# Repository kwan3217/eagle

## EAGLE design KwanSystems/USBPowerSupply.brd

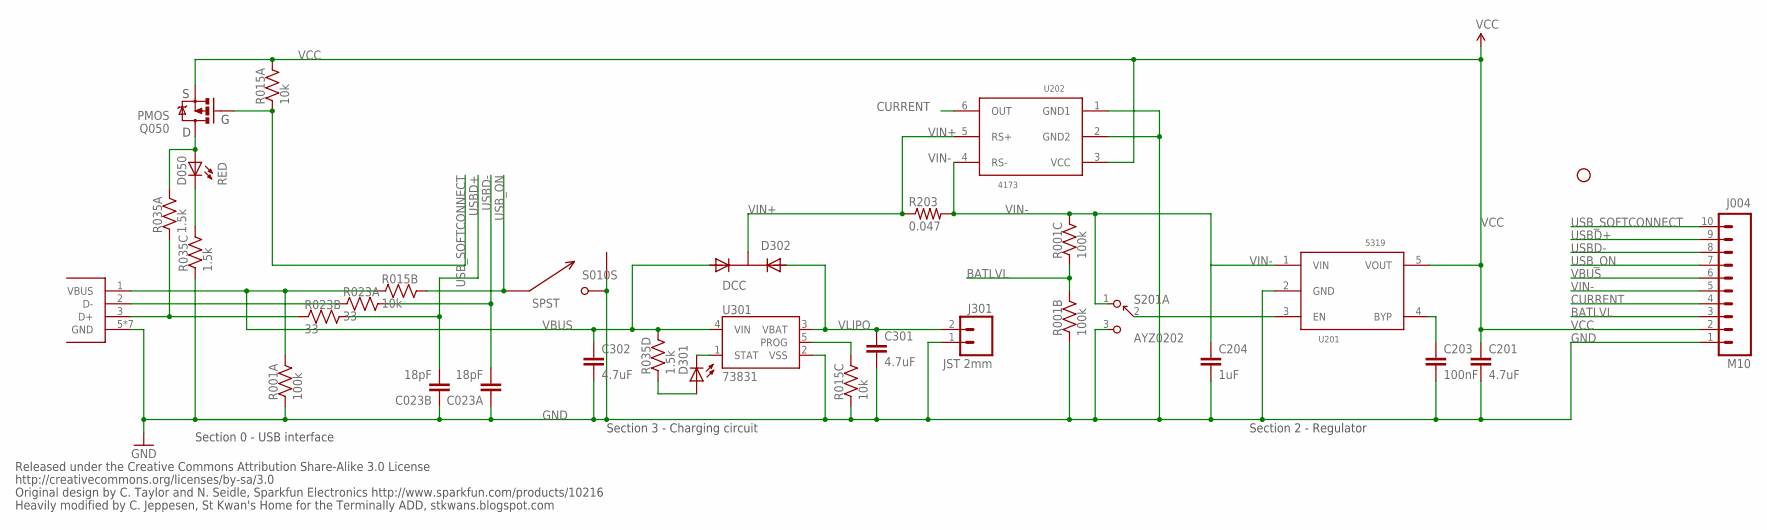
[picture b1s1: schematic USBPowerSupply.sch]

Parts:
C023: 18pF; CKCM25
C201, C301, C302: 4.7uF; 0402-CAP
C203: 100nF; 0402-CAP
C204: 1uF; 0402-CAP
D050, D301: RED; LED-0603
D302: DCC; SOT-23-3
J001: USB_MICROB_JSTGCT; USB_MICROB_3075
J004: M10; 1X10
J301: JST 2mm; JST-2-SMD
JP1: STAND-OFF
Q050: PMOS; SOT23-3
R001: 100k; CRA04
R015: 10k; CRA04
R023: 33; CRA02
R035: 1.5k; CRA04
R203: 0.047; 0402-RES
S010: SPST; B3U-1100P
S201: AYZ0202
U201: 5319; SOT-23-5
U202: 4173; SOT-23-6
U301: 73831; SOT23-5

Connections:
BATLVL: J004.3, R001.3 (1), R001.7 (2)
CONN_D+: J001.3 (D+), R023.2 (1), R035.1
CONN_D-: J001.2 (D-), R023.1
CURRENT: J004.4, U202.6 (OUT)
GND: C023.1, C023.2 (1), C201.2, C203.2, C204.2, C301.2, C302.2, J001.5 (GND), J001.P$1 (GND), J001.P$2 (GND), J001.P$3 (GND), J001.P$4 (GND), J001.P$8 (GND), J001.P$10 (GND), J004.1, J301.1, R001.1, R001.2 (1), R015.3 (1), R035.3 (1), S010.P$2 (2), S010.P$3 (1), S201.3, U201.2 (GND), U202.1 (GND1), U202.2 (GND2), U301.2 (VSS)
unnamed: D301.A, R035.4 (1)
unnamed: R015.6 (2), U301.5 (PROG)
unnamed: D301.C, U301.1 (STAT)
unnamed: S201.2, U201.3 (EN)
unnamed: D050.A, Q050.3 (D), R035.8 (2)
unnamed: D050.C, R035.6 (2)
unnamed: C203.1, U201.4 (BYP)
USBD+: C023.3 (2), J004.9, R023.3 (2)
USBD-: C023.4 (2), J004.8, R023.4 (2)
USB_ON: J004.7, R015.7 (2), S010.P$1 (1)
USB_SOFTCONNECT: J004.10, Q050.1 (G), R015.1
VBUS: C302.1, D302.1 (A1), J001.1 (VBUS), J004.6, R001.8 (2), R015.2 (1), R035.5 (2), U301.4 (VIN)
VCC: C201.1, J004.2, Q050.2 (S), R015.8 (2), U201.5 (VOUT), U202.3 (VCC)
VIN+: D302.3 (K), R203.1, U202.5 (RS+)
VIN-: C204.1, J004.5, R001.6 (2), R203.2, S201.1, U201.1 (VIN), U202.4 (RS-)
VLIPO: C301.1, D302.2 (A2), J301.2, U301.3 (VBAT)

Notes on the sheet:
Section 2 - Regulator
Section 3 - Charging circuit
Section 0 - USB interface
Released under the Creative Commons Attribution Share-Alike 3.0 License
http://creativecommons.org/licenses/by-sa/3.0
Original design by C. Taylor and N. Seidle, Sparkfun Electronics http://www.sparkfun.com/products/10216
Heavily modified by C. Jeppesen, St Kwan's Home for the Terminally ADD, stkwans.blogspot.com

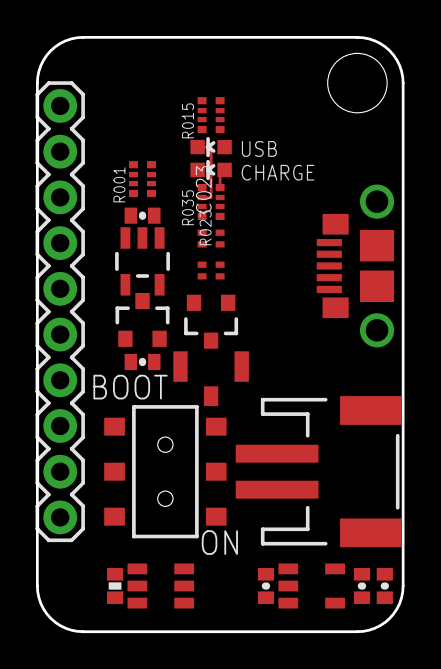
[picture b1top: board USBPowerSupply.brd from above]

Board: 2 copper layers, 20.3 x 33.0 mm, 24 parts (0 on the bottom side), 21 nets.

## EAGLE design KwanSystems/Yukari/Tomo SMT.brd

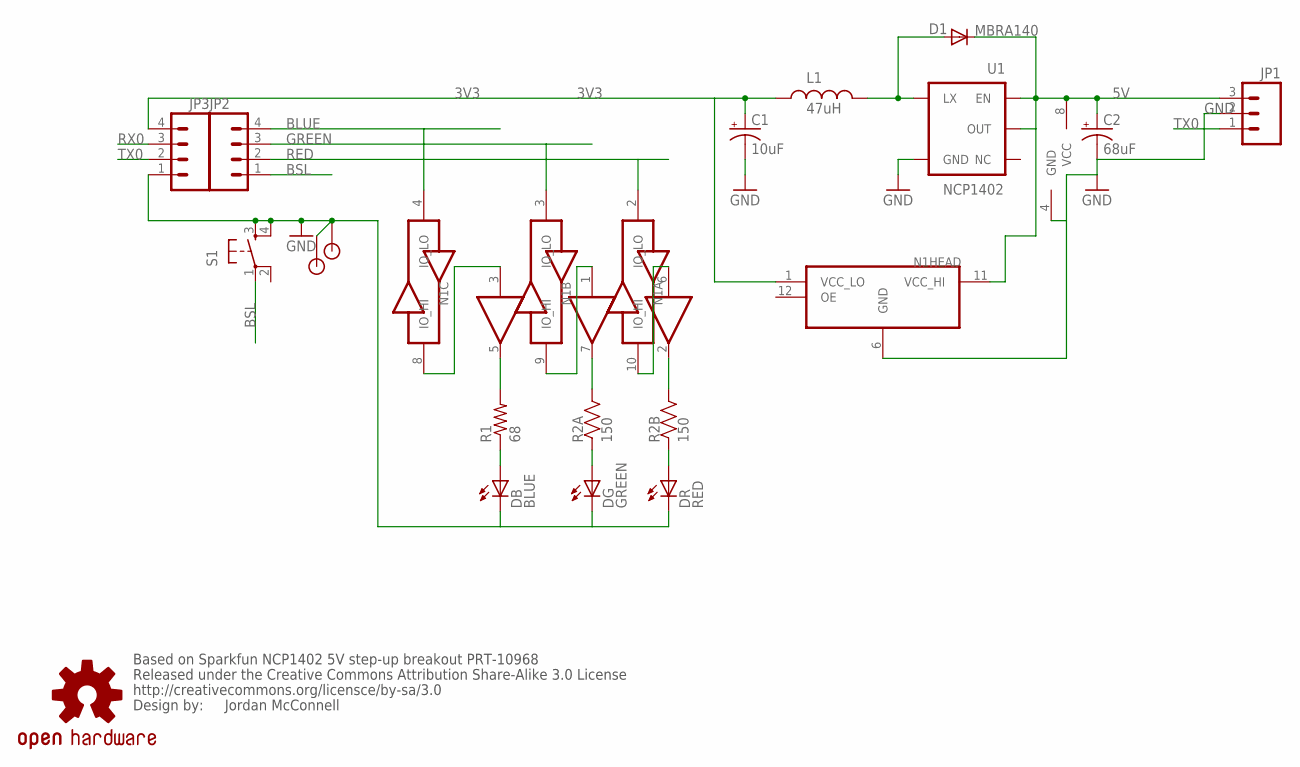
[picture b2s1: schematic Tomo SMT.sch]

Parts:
C1: 10uF; EIA3216
C2: 68uF; EIA3528
D1: MBRA140; SMA-DIODE
DB: BLUE; LED5MM
DG: GREEN; LED5MM
DR: RED; LED5MM
JP1: M03PTH; 1X03
JP2, JP3: M04PTH; 1X04
L1: 47uH; RADIAL_5MM
N1: TXB0104RUT; R-PUQFN-N12
R1: 68; 0402-RES
R2: 150; CRA02
S1: TAC_SWITCHPTH; TACTILE-PTH
U1: NCP1402; SOT23-5
U$1: OSHW-LOGOL; OSHW-LOGO-L
U$2: 743G34; DCT
U$3, U$4: STANDOFF

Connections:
3V3: C1.A (+), JP3.4, L1.1, N1.1 (VCC_LO)
5V: C2.A (+), D1.C, JP1.3, N1.11 (VCC_HI), U1.1 (EN), U1.2 (OUT), U$2.8 (VCC)
BLUE: JP2.4, N1.4 (IO_LO)
BSL: JP2.1, S1.1
GND: C1.C (-), C2.C (-), DB.K (C), DG.K (C), DR.K (C), JP1.2, JP3.1, N1.6 (GND), S1.3, S1.4, U1.4 (GND), U$2.4 (GND), U$3.P$1, U$4.P$1
GREEN: JP2.3, N1.3 (IO_LO)
unnamed: R1.2, U$2.5 (OUT)
unnamed: DB.A, R1.1
unnamed: D1.A, L1.2, U1.5 (LX)
unnamed: DG.A, R2.1
unnamed: R2.4 (2), U$2.7 (OUT)
unnamed: R2.3 (2), U$2.2 (OUT)
unnamed: DR.A, R2.2 (1)
unnamed: N1.8 (IO_HI), U$2.3 (IN)
unnamed: N1.9 (IO_HI), U$2.1 (IN)
unnamed: N1.10 (IO_HI), U$2.6 (IN)
RED: JP2.2, N1.2 (IO_LO)
RX0: JP3.3
TX0: JP1.1, JP3.2

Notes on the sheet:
Jordan McConnell
Based on Sparkfun NCP1402 5V step-up breakout PRT-10968
Released under the Creative Commons Attribution Share-Alike 3.0 License
http://creativecommons.org/licensce/by-sa/3.0
Design by:

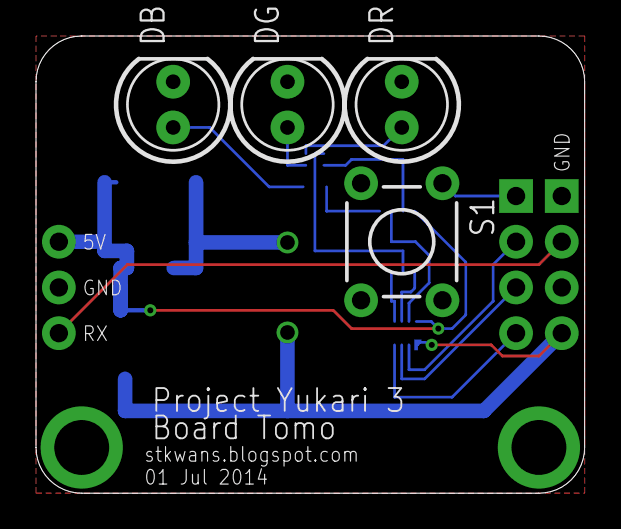
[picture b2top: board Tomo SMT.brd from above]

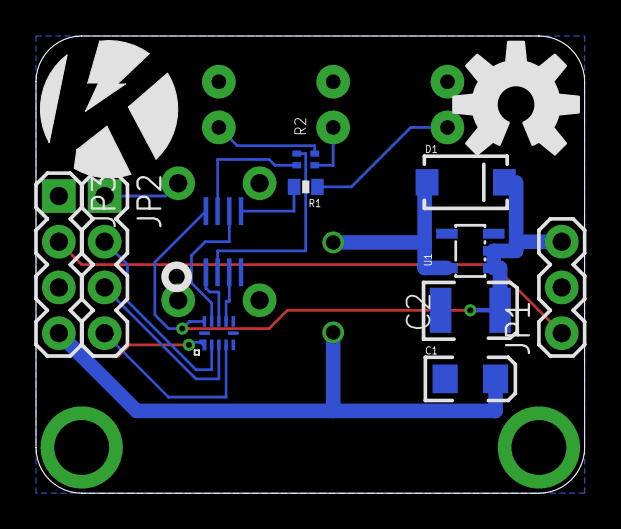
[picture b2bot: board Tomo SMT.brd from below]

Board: 2 copper layers, 30.5 x 25.4 mm, 20 parts (14 on the bottom side), 18 nets.

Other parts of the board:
U$7: KWAN_CIRCLE

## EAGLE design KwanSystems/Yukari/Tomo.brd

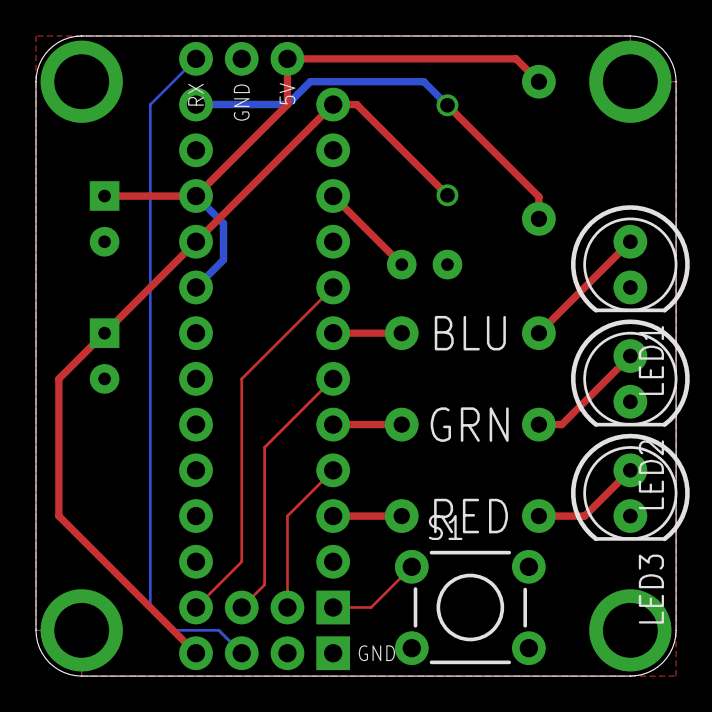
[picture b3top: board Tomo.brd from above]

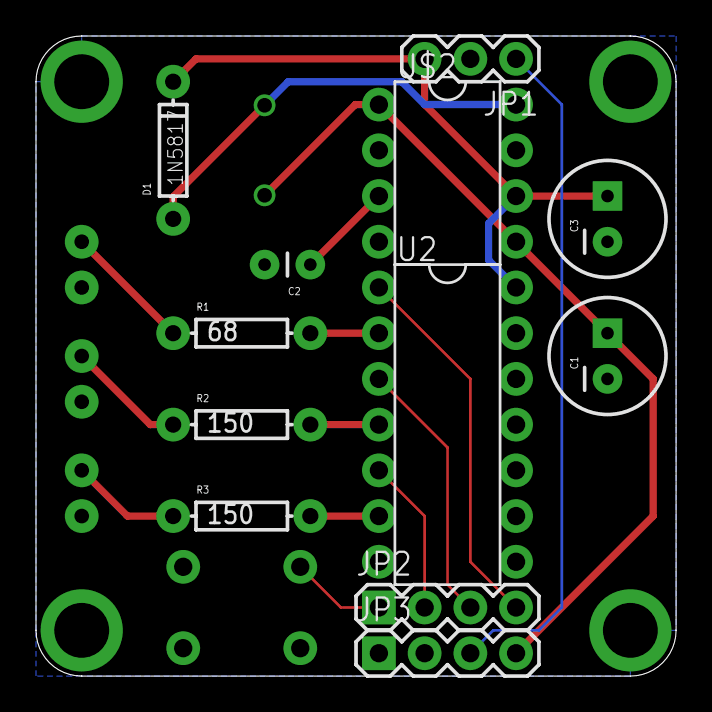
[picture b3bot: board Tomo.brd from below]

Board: 2 copper layers, 35.6 x 35.6 mm, 23 parts (13 on the bottom side), 16 nets.

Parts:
C1: 150uF; CPOL-RADIAL-100UF-25V
C2: 100nF; CAP-PTH-SMALL
C3: 100uF; CPOL-RADIAL-100UF-25V
D1: 1N5817; DIODE-1N4148
JP1: 1X03
JP2, JP3: 1X04
L1: 22uH; RADIAL_5MM
LED1: BLUE; LED5MM
LED2: GREEN; LED5MM
LED3: RED; LED5MM
R1: 68; AXIAL-0.3
R2, R3: 150; AXIAL-0.3
S1: TACTILE-PTH
U2: 741034; DIL-14
U$1: OSHW-LOGOL; OSHW-LOGO-L
U$2: MAX756; DIL-8
U$3, U$4, U$5, U$6: STANDOFF
U$7: KWAN_CIRCLE

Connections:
3V3: C1.1, JP3.4, L1.1, U$2.1, U$2.5
5V: C3.1, D1.C, JP1.3, U2.14, U$2.6
BLUE: JP2.4, U2.1
BSL: JP2.1, S1.1
GND: C1.2, C2.2, C3.2, JP1.2, JP3.1, LED1.K, LED2.K, LED3.K, S1.3, S1.4, U2.7, U2.9, U2.11, U2.13, U$2.2, U$2.7, U$3.P$1, U$4.P$1, U$5.P$1, U$6.P$1
GREEN: JP2.3, U2.3
unnamed: LED1.A, R1.P$1
unnamed: LED2.A, R2.P$1
unnamed: D1.A, L1.2, U$2.8
unnamed: LED3.A, R3.P$1
unnamed: R1.P$2, U2.2
unnamed: R2.P$2, U2.4
unnamed: R3.P$2, U2.6
unnamed: C2.1, U$2.3
RED: JP2.2, U2.5
TX0: JP1.1, JP3.3

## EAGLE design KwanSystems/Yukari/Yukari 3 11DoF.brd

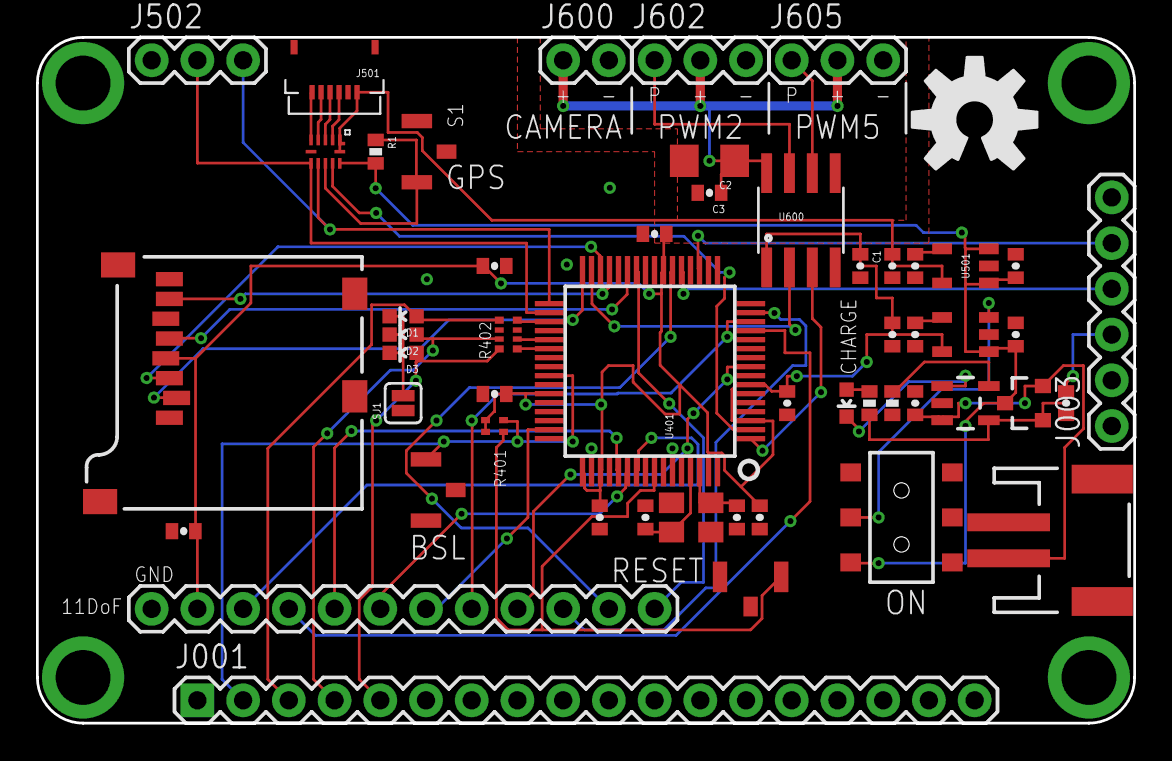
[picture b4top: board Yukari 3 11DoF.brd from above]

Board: 2 copper layers, 61.0 x 38.1 mm, 58 parts (1 on the bottom side), 53 nets.

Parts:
C1, C3, C204, C407, C423, C432, C443, C451, C463, C504, C701: 100nF; 0402-CAP
C2: 10uF; 1206
C201, C501: 1uF; 0402-CAP
C205, C301, C302, C505: 4.7uF; 0402-CAP
C461, C462: 18pF; 0402-CAP
D1, D301: RED; LED-0603
D2: GREEN; LED-0603
D3: BLUE; LED-0603
D302: DCC; SOT-23-3
J001: M06; 1X18
J003: M06; 1X06
J301: JST 2mm; JST-2-SMD
J406: 11DoF; 1X12
J501: GP-2106
J502, J602, J605: 1X03
J600: M02PTH; 1X02
JP1, JP2, JP3, JP4: STANDOFF
R1, R301: 10k; 0402-RES
R302: 1.5k; 0402-RES
R401: CRA02
R402: 150; CRA04
S1, S420, S457: SPST; B3U-1100P
S201: SPDT; AYZ0202
SJ1: SOLDERJUMPERNC; SJ_2S
U201: 5319; SOT-23-5
U301: 73831; SOT23-5
U401: LPC2148; LQFP64
U501: 5319 1.8V; SOT-23-5
U502: TXB0104RUT; R-PUQFN-N12
U600: ADUM3221; SO8N
U701: MICROSD-SOCKET; MICROSD-SOCKET-PP
U$1: KWAN_CIRCLE
U$2: OSHW-LOGO-L
Y401: 12M; CRYSTAL_SMD

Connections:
1.8V: C505.1, J501.VCC, U501.5, U502.1, U502.12
1PPS_I: J501.1PPS, U502.2
BLUE: R402.1, U401.38
BLUE-: D3.A, J001.5, R402.8
BSL: J001.2, R401.4, S420.P$2, U401.41
CHG_PROG: R301.2, U301.5
CS0: U401.32, U701.2
CSA: J406.10, U401.55
CSG: J406.4, U401.9
EN: S201.2, U201.3
GND: C1.2, C201.2, C204.2, C205.2, C301.2, C302.2, C407.2, C423.2, C432.2, C443.2, C451.2, C461.1, C462.1, C463.2, C501.2, C504.2, C505.2, C701.2, J001.1, J003.1, J301.1, J406.12, J501.GND, J502.1, JP1.P$1, JP2.P$1, JP3.P$1, JP4.P$1, R301.1, S1.P$2, S1.P$3, S201.3, S420.P$1, S420.P$3, S457.P$1, S457.P$3, SJ1.1, U201.2, U301.2, U401.6, U401.18, U401.25, U401.42, U401.50, U401.59, U501.2, U502.6, U600.4, U701.6, U701.CD2, U701.GND1, U701.GND3, Y401.2, Y401.4
GREEN: R402.2, U401.37
GREEN-: D2.A, J001.4, R402.7
HV: C2.1, C3.1, J600.1, J602.2, J605.2, U600.8
HV-GND: C2.2, C3.2, J600.2, J602.3, J605.3, U600.5
IA: J406.9, U401.13
IC: J406.3, U401.15
IG: J406.5, U401.14
MISO0: U401.29, U701.7
MISO1: J406.8, U401.53
MOSI0: U401.30, U701.3
MOSI1: J406.7, U401.54
unnamed: D1.C, D2.C, D3.C, SJ1.2
unnamed: C504.1, U501.4
unnamed: C204.1, U201.4
ONOFF: R1.1, S1.P$1, U502.9
ONOFF_I: J501.ONOFF, U502.3
PPS: U401.2, U502.10
PWM2: U401.31, U600.2
PWM5: U401.1, U600.3
QWM2: J602.1, U600.7
QWM5: J605.1, U600.6
RED: R402.4, U401.35
RED-: D1.A, J001.3, R402.5
RST: R401.3, S457.P$2, U401.57
RX0: J003.4, U401.21
RX1: J502.2, U401.34, U502.7
RX_I: J501.RX, U502.4
SCK0: U401.27, U701.5
SCK1: J406.6, U401.47
SCL0: J406.2, U401.22
SDA0: J406.1, U401.26
STAT+: D301.A, R302.1
STAT-: D301.C, U301.1
TX0: J003.5, U401.19
TX1: J502.3, U401.33, U502.8
TX_O: J501.TX, U502.5
VBUS: C302.1, D302.1, J003.3, R302.2, U301.4
VCC: C1.1, C205.1, C407.1, C423.1, C432.1, C443.1, C451.1, C463.1, C701.1, J406.11, R401.1, R401.2, U201.5, U401.3, U401.7, U401.23, U401.43, U401.49, U401.51, U401.63, U600.1, U701.4
VIN: C201.1, C501.1, D302.3, R1.2, S201.1, U201.1, U501.1, U501.3, U502.11
VLIPO: C301.1, D302.2, J301.2, U301.3
XTAL1: C462.2, U401.62, Y401.3
XTAL2: C461.2, U401.61, Y401.1

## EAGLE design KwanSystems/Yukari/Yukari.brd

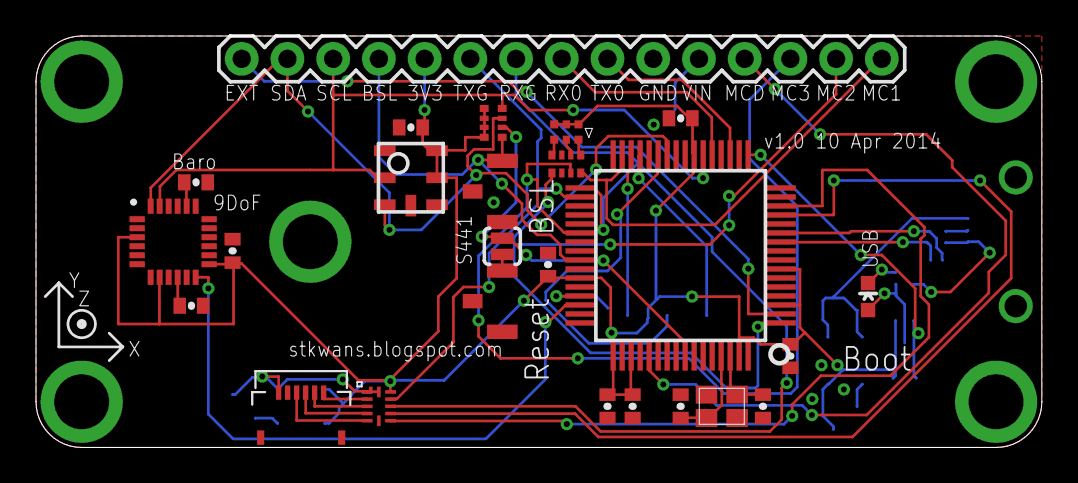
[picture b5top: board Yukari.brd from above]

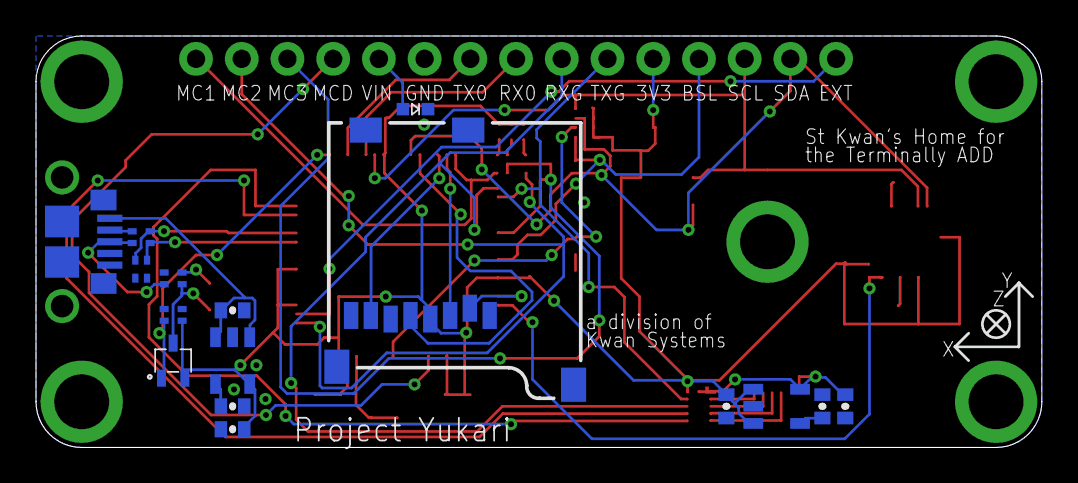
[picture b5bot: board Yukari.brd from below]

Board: 2 copper layers, 55.9 x 22.9 mm, 47 parts (16 on the bottom side), 46 nets.

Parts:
C023: 22pF; CKCM25
C101, C204, C443, C449, C504, C610, C613: 100nF; 0402-CAP
C201, C423, C451, C463, C501: 1uF; 0402-CAP
C205, C505: 4.7uF; 0402-CAP
C461, C462: 33pF; 0402-CAP
C620: 2.2nF; 0402-CAP
D050: BLUE; LED-0603
D401: SMLP36
D402: D0603
J001: USB_MICROB_JSTGCT; USB_MICROB_3075
J401: 1X15
J501: GP-2106
J701: MICROSD-SOCKET; MICROSD-SOCKET-PP
JP1, JP2, JP3, JP4, JP5: STANDOFF
Q050: PMOS; SC-70-3
R015: 10k; CRA02
R023: 33; CRA02
R053: 1.5k; CRA02
R401: 10k; CRA04
R402: 1.5k; CRA04
S441, S457: B3U-1100P
S457A: SOLDERJUMPERNO; SJ_2S-NO
U101: BMP180
U201: 5319 3.3V; SOT-23-5
U401: LPC2148; LQFP64
U501: 5319 1.8V; SOT-23-5
U502: TXB0104RUT; R-PUQFN-N12
U601: MPU9150; LLGA24
U$4: AXES
Y401: 12MHz; CRYSTAL_SMD_2MM_2_5MM

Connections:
1.8V: C505.1, J501.VCC, U501.5, U502.1, U502.12
1PPS_I: J501.1PPS, U502.5
ACCINT: U401.46, U601.12
BSL: J401.12, R401.1, S441.P$1, U401.41
CONN_D+: J001.3, R023.2, R053.4
CONN_D-: J001.2, R023.1
CS0: J701.2, U401.45
EXT: J401.15, U401.2
GND: C023.3, C023.4, C101.2, C201.2, C204.2, C205.2, C423.2, C443.2, C449.1, C451.2, C461.1, C462.1, C463.2, C501.2, C504.2, C505.2, C610.2, C613.1, C620.1, J001.5, J001.P$1, J001.P$2, J001.P$3, J001.P$4, J001.P$8, J001.P$10, J401.6, J501.GND, J701.6, J701.CD2, J701.GND1, J701.GND3, JP1.P$1, JP2.P$1, JP3.P$1, JP4.P$1, JP5.P$1, R053.3, S441.P$2, S441.P$3, S457.P$2, S457.P$3, U101.7, U201.2, U401.6, U401.18, U401.25, U401.42, U401.50, U401.59, U501.2, U502.6, U601.1, U601.9, U601.11, U601.15, U601.17, U601.18, Y401.2, Y401.4
MCD: J401.4, U401.53
MISO0: J701.7, U401.29
MOSI0: J701.3, U401.30
unnamed: C620.2, U601.20
unnamed: S457.P$1, S457A.2
unnamed: C504.1, U501.4
unnamed: C610.1, U601.10
unnamed: C204.1, U201.4
ONOFF: U401.13, U502.8
ONOFF_I: J501.ONOFF, U502.4
PPS: U401.14, U502.7
PWMB/MC1: J401.1, R402.8, U401.31
PWMG/MC2: J401.2, R402.5, U401.1
PWMR/MC3: J401.3, R402.7, U401.38
QWMB: D401.1, R402.1
QWMG: D401.5, R402.4
QWMR: D401.3, R402.2
RESET: R401.2, S457A.1, U401.57
RX0: J401.8, U401.21
RX_GPS: J401.9, U401.33, U502.9
RX_I: J501.RX, U502.3
SCK0: J701.5, U401.27
SCL0: J401.13, R401.4, U101.5, U401.22, U601.23
SDA0: J401.14, R401.3, U101.6, U401.26, U601.24
TX0: J401.7, U401.19
TX_GPS: J401.10, U401.34, U502.10
TX_O: J501.TX, U502.2
USBD+: C023.1, R023.3, U401.10
USBD-: C023.2, R023.4, U401.11
USB_CONNECT+: D050.A, Q050.3, R053.1
USB_LED-: D050.C, R053.2
USB_SOFTCONNECT: Q050.1, R015.4, U401.17
VBUS: C201.1, J001.1, U201.1, U201.3
VCC: C101.1, C205.1, C423.1, C443.1, C449.2, C451.1, C463.1, C501.1, C613.2, D401.2, D401.4, D401.6, J401.11, J701.4, Q050.2, R015.1, R401.5, R401.6, R401.7, R401.8, U101.2, U101.3, U201.5, U401.3, U401.7, U401.23, U401.43, U401.49, U401.51, U401.63, U501.1, U501.3, U502.11, U601.3, U601.8, U601.13
VEXT: D402.A, J401.5
XTAL1: C462.2, U401.62, Y401.1
XTAL2: C461.2, U401.61, Y401.3

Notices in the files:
parts and their libraries:
SparkFun-Connectors: Licensing: CC v3.0 Share-Alike You are welcome to use this library for commercial purposes.
